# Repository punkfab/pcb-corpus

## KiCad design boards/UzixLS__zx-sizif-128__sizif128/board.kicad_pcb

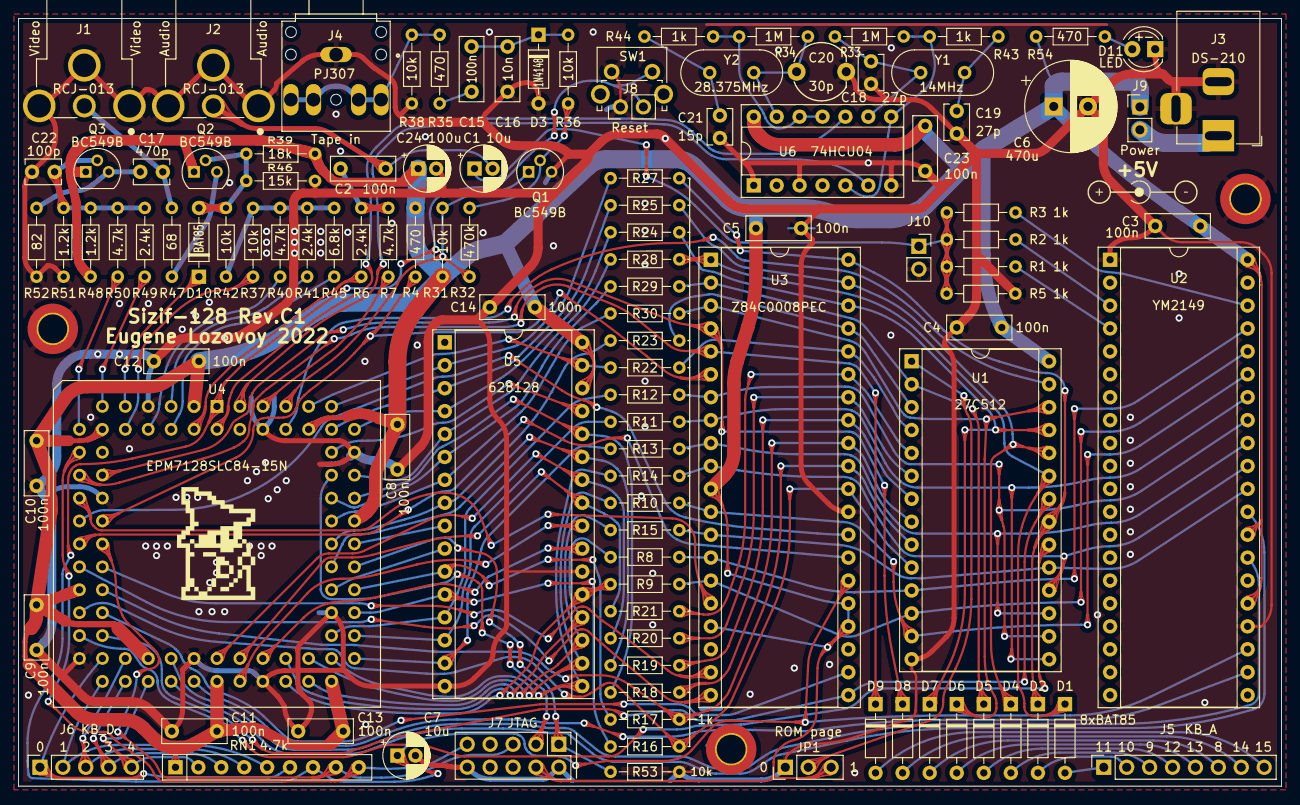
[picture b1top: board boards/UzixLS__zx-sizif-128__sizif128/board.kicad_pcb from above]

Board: 2 copper layers, 140.0 x 85.1 mm, 117 parts (0 on the bottom side), 121 nets.

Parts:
C1, C7: 10u; CP_Radial_D5.0mm_P2.00mm
C2, C3, C4, C5, C8, C9, C10, C11, C12, C13, C14, C15, C23: 100n; C_Disc_D7.0mm_W2.5mm_P5.00mm
C6: 470u; CP_Radial_D10.0mm_P3.80mm
C16: 10n; C_Disc_D7.0mm_W2.5mm_P5.00mm
C17: 470p; C_Disc_D3.8mm_W2.6mm_P2.50mm
C18, C19: 27p; C_Disc_D3.8mm_W2.6mm_P2.50mm
C20: 30p; C_Trim_D6.3mm_P5.50mm
C21: 15p; C_Disc_D3.8mm_W2.6mm_P2.50mm
C22: 100p; C_Disc_D3.8mm_W2.6mm_P2.50mm
C24: 100u; CP_Radial_D5.0mm_P2.00mm
D1, D2, D4, D5, D6, D7, D8, D9, D10: BAT85; D_DO-35_SOD27_P7.62mm_Horizontal
D3: 1N4148; D_DO-35_SOD27_P7.62mm_Horizontal
D11: LED; LED_D4.0mm
H1, H2, H3: MountingHole; MountingHole_3.2mm_M3_DIN965_Pad_TopOnly
J1, J2: RCJ-013; CUI_RCJ-013
J3: DS-210; BarrelJack_Horizontal
J4: PJ307; SWITCHCRAFT_35RAPC4BHN2
J5: Conn_01x08; PinSocket_1x08_P2.54mm_Vertical
J6: Conn_01x05; PinSocket_1x05_P2.54mm_Vertical
J7: Conn_02x05; PinHeader_2x05_P2.54mm_Vertical
J8, J9: Conn_01x02; PinHeader_1x02_P2.54mm_Vertical
J10: Conn_01x02_Female; PinSocket_1x02_P2.54mm_Vertical
JP1: Jumper_3_Bridged12; PinHeader_1x03_P2.54mm_Vertical
LOGO1: logo; black-mage-12.5x8.6-r
LOGO2: logo; dc_center_positive_big
Q1, Q2, Q3: BC549B; TO-92
R1, R2, R3, R5, R8, R9, R10, R11, R12, R13, R14, R15, R16, R17, R18, R19, R20, R21, R22, R23, R24, R25, R27, R28, R29, R30, R43, R44: 1k; R_Axial_DIN0204_L3.6mm_D1.6mm_P7.62mm_Horizontal
R4, R35, R54: 470; R_Axial_DIN0204_L3.6mm_D1.6mm_P7.62mm_Horizontal
R6, R41, R49: 2.4k; R_Axial_DIN0204_L3.6mm_D1.6mm_P7.62mm_Horizontal
R7, R40, R50: 4.7k; R_Axial_DIN0204_L3.6mm_D1.6mm_P7.62mm_Horizontal
R31, R36, R37, R38, R42, R53: 10k; R_Axial_DIN0204_L3.6mm_D1.6mm_P7.62mm_Horizontal
R32: 470k; R_Axial_DIN0204_L3.6mm_D1.6mm_P7.62mm_Horizontal
R33, R34: 1M; R_Axial_DIN0204_L3.6mm_D1.6mm_P7.62mm_Horizontal
R39: 18k; R_Axial_DIN0204_L3.6mm_D1.6mm_P7.62mm_Horizontal
R45: 6.8k; R_Axial_DIN0204_L3.6mm_D1.6mm_P7.62mm_Horizontal
R46: 15k; R_Axial_DIN0204_L3.6mm_D1.6mm_P7.62mm_Horizontal
R47: 68; R_Axial_DIN0204_L3.6mm_D1.6mm_P7.62mm_Horizontal
R48, R51: 1.2k; R_Axial_DIN0204_L3.6mm_D1.6mm_P7.62mm_Horizontal
R52: 82; R_Axial_DIN0204_L3.6mm_D1.6mm_P7.62mm_Horizontal
RN1: 4.7k; R_Array_SIP9
SW1: SW_Push; SW_Tactile_SPST_Angled_PTS645Vx83-2LFS
U1: 27C512; DIP-28_W15.24mm_Socket
U2: YM2149; DIP-40_W15.24mm_Socket
U3: Z84C0008PEC; DIP-40_W15.24mm_Socket
U4: EPM7128SLC84-15N; PLCC-84_THT-Socket
U5: 628128; DIP-32_W15.24mm_Socket
U6: 74HCU04; DIP-14_W7.62mm_Socket
Y1: 14MHz; Crystal_HC49-U_Vertical
Y2: 28.375MHz; Crystal_HC49-U_Vertical

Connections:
+5V: C3.2, C4.2, C5.2, C6.1, C8.2, C9.2, C10.2, C11.2, C12.2, C13.2, C14.2, C23.2, C24.1, J7.4, J9.1, JP1.3 (B), Q2.1 (C), Q3.1 (C), R4.2, R31.1, R39.2, R48.1, R54.1, RN1.1 (common), U1.28 (VCC), U2.25 (A8), U2.28 (BC2), U2.40 (VCC), U3.11 (VCC), U3.17 (~NMI), U3.24 (~WAIT), U3.25 (~BUSRQ), U4.3 (VCCINT), U4.13 (VCCIO), U4.26 (VCCIO), U4.38 (VCCIO), U4.43 (VCCINT), U4.53 (VCCIO), U4.66 (VCCIO), U4.78 (VCCIO), U5.30 (CS2), U5.32 (VCC), U6.14 (VCC)
A0: R16.1, U1.10 (A0), U3.30 (A0), U4.28 (IO)
A1: R17.1, U1.9 (A1), U3.31 (A1), U4.27 (IO)
A2: R18.1, U1.8 (A2), U3.32 (A2)
A3: R19.1, U1.7 (A3), U3.33 (A3)
A4: R20.1, U1.6 (A4), U3.34 (A4)
A5: R21.1, U1.5 (A5), U3.35 (A5)
A6: R22.1, U1.4 (A6), U3.36 (A6)
A7: R23.1, U1.3 (A7), U3.37 (A7)
A8: D7.1 (K), R24.1, U1.25 (A8), U3.38 (A8)
A9: D4.1 (K), R25.1, U1.24 (A9), U3.39 (A9)
A10: D2.1 (K), R27.1, U1.21 (A10), U3.40 (A10)
A11: D1.1 (K), R28.1, U1.23 (A11), U3.1 (A11)
A12: D5.1 (K), R29.1, U1.2 (A12), U3.2 (A12)
A13: D6.1 (K), R30.1, U1.26 (A13), U3.3 (A13)
A14: D8.1 (K), U3.4 (A14), U4.17 (IO)
A15: D9.1 (K), U3.5 (A15), U4.16 (IO)
AY_BC1: U2.29 (BC1), U4.39 (IO)
AY_BDIR: U2.27 (BDIR), U4.40 (IO)
AY_CLK: U2.22 (CLOCK), U4.41 (IO)
BEEPER: R6.1, U4.4 (IO)
Blue: R37.1, U4.10 (IO)
Bright: R45.1, U4.6 (IO)
CHROMA0: R50.1, U4.12 (IO)
CHROMA1: R49.1, U4.11 (IO)
CLK14: U4.83 (INPUT/GCLK1), U6.6
CLKCPU: R4.1, U3.6 (~CLK), U4.21 (IO)
CLK_PAL: U4.2 (INPUT/OE2/GCLK2), U6.10
Csync: D10.1 (K), U4.9 (IO)
D0: R8.1, U1.11 (D0), U2.37 (DA0), U3.14 (D0)
D1: R9.1, U1.12 (D1), U2.36 (DA1), U3.15 (D1)
D2: R10.1, U1.13 (D2), U2.35 (DA2), U3.12 (D2)
D3: R11.1, U1.15 (D3), U2.34 (DA3), U3.8 (D3)
D4: R12.1, U1.16 (D4), U2.33 (DA4), U3.7 (D4)
D5: R13.1, U1.17 (D5), U2.32 (DA5), U3.9 (D5)
D6: R14.1, U1.18 (D6), U2.31 (DA6), U3.10 (D6)
D7: R15.1, U1.19 (D7), U2.30 (DA7), U3.13 (D7)
GND: C3.1, C4.1, C5.1, C6.2, C7.2, C8.1, C9.1, C10.1, C11.1, C12.1, C13.1, C14.1, C16.1, C18.1, C19.1, C20.2, C21.1, C22.2, C23.1, C24.2, D3.2 (A), D11.1 (K), H1.1, H2.1, H3.1, J1.2 (Ext), J2.2 (Ext), J3.2, J3.3, J4.S, J7.2, J7.10, J8.1, J10.2, JP1.1 (A), Q1.3 (E), R5.1, R38.1, R46.2, R51.1, R52.1, R53.1, SW1.1, U1.14 (GND), U2.1 (VSS), U2.24 (~A9), U3.29 (GND), U4.7 (GNDIO), U4.19 (GNDIO), U4.32 (GNDIO), U4.42 (GNDINT), U4.47 (GNDIO), U4.59 (GNDIO), U4.72 (GNDIO), U4.82 (GNDINT), U5.16 (GND), U5.22 (~CS1), U6.1, U6.3, U6.7 (GND)
Green: R41.1, U4.5 (IO)
KD0: J6.1, RN1.6 (R5), U4.34 (IO)
KD1: J6.2, RN1.5 (R4), U4.33 (IO)
KD2: J6.3, RN1.4 (R3), U4.36 (IO)
KD3: J6.4, RN1.3 (R2), U4.35 (IO)
KD4: J6.5, RN1.2 (R1), U4.37 (IO)
unnamed: C1.1, J10.1, R1.2, R2.2, R3.2, R5.2
unnamed: C2.1, R6.2, R7.2
unnamed: C15.1, R35.2
unnamed: C15.2, C16.2, D3.1 (K), R36.1
unnamed: C17.1, Q3.3 (E), R52.2
unnamed: C18.2, R33.1, U6.9, Y1.1
unnamed: C19.2, R43.1, Y1.2
unnamed: C20.1, R34.1, U6.13, Y2.1
unnamed: C21.2, R44.1, Y2.2
unnamed: C22.1, Q3.2 (B), R48.2, R49.2, R50.2, R51.2
unnamed: D1.2 (A), J5.1
unnamed: D2.2 (A), J5.2
unnamed: D4.2 (A), J5.3
unnamed: D5.2 (A), J5.4
unnamed: D6.2 (A), J5.5
unnamed: D7.2 (A), J5.6
unnamed: D8.2 (A), J5.7
unnamed: D9.2 (A), J5.8
unnamed: D10.2 (A), Q2.2 (B), R39.1, R42.2, R46.1
unnamed: D11.2 (A), R54.2
unnamed: J3.1, J9.2
unnamed: JP1.2 (C), U1.1 (A15)
unnamed: Q1.2 (B), R32.2, R36.2
unnamed: Q2.3 (E), R47.2
unnamed: R1.1, U2.4 (A)
unnamed: R2.1, U2.3 (B)
unnamed: R3.1, U2.38 (C)
unnamed: R33.2, R43.2, U6.5, U6.8
unnamed: R34.2, R44.2, U6.11, U6.12
unnamed: R37.2, R40.2, R41.2, R42.1, R45.2
RA14: U1.27 (A14), U4.80 (IO)
Red: R40.1, U4.8 (IO)
SOUND: C1.2, C2.2, J2.1 (In)
TAPE_IN: J4.R, J4.RN, J4.T, J4.TN, R35.1, R38.2
TAPE_IN0: Q1.1 (C), R31.2, R32.1, U4.79 (IO)
TAPE_OUT: R7.1, U4.81 (IO)
TCK: J7.1, R53.2, U4.62 (IO/TCK)
TDI: J7.9, RN1.9 (R8), U4.14 (IO/TDI)
TDO: J7.3, U4.71 (IO/TDO)
TMS: J7.5, RN1.8 (R7), U4.23 (IO/TMS)
VA0: R16.2, U4.58 (IO), U5.12 (A0)
VA1: R17.2, U4.60 (IO), U5.11 (A1)
VA2: R18.2, U4.68 (IO), U5.28 (A13)
VA3: R19.2, U4.63 (IO), U5.27 (A8)
VA4: R20.2, U4.44 (IO), U5.26 (A9)
VA5: R21.2, U4.46 (IO), U5.25 (A11)
VA6: R22.2, U4.77 (IO), U5.31 (A15)
VA7: R23.2, U4.65 (IO), U5.8 (A4)
VA8: R24.2, U4.74 (IO), U5.4 (A12)
VA9: R25.2, U4.76 (IO), U5.3 (A14)
VA10: R27.2, U4.75 (IO), U5.2 (A16)
VA11: R28.2, U4.70 (IO), U5.5 (A7)
VA12: R29.2, U4.69 (IO), U5.6 (A6)
VA13: R30.2, U4.67 (IO), U5.7 (A5)
VA14: U4.61 (IO), U5.10 (A2)
VA15: U4.64 (IO), U5.9 (A3)
VA16: U4.48 (IO), U5.23 (A10)
VD0: R8.2, U4.50 (IO), U5.20 (Q6)
VD1: R9.2, U4.49 (IO), U5.21 (Q7)
VD2: R10.2, U4.52 (IO), U5.18 (Q4)
VD3: R11.2, U4.56 (IO), U5.14 (Q1)
VD4: R12.2, U4.57 (IO), U5.13 (Q0)
VD5: R13.2, U4.54 (IO), U5.15 (Q2)
VD6: R14.2, U4.55 (IO), U5.17 (Q3)
VD7: R15.2, U4.51 (IO), U5.19 (Q5)
VIDEO: C17.2, J1.1 (In), R47.1
nINT: U3.16 (~INT), U4.18 (IO)
nIORQ: U3.20 (~IORQ), U4.24 (IO)
nM1: U3.27 (~M1), U4.22 (IO)
nMREQ: U3.19 (~MREQ), U4.25 (IO)
nRD: U1.22 (~OE), U3.21 (~RD), U4.31 (IO)
nRFSH: U3.28 (~RFSH), U4.20 (IO)
nROMCS: U1.20 (~CE), U4.30 (IO)
nRST: C7.1, J8.2, RN1.7 (R6), SW1.2, U2.23 (~RESET), U3.26 (~RESET), U4.1 (INPUT/GCLRN)
nVRD: U4.45 (IO), U5.24 (~OE)
nVWR: U4.73 (IO), U5.29 (~WE)
nWR: U3.22 (~WR), U4.29 (IO)

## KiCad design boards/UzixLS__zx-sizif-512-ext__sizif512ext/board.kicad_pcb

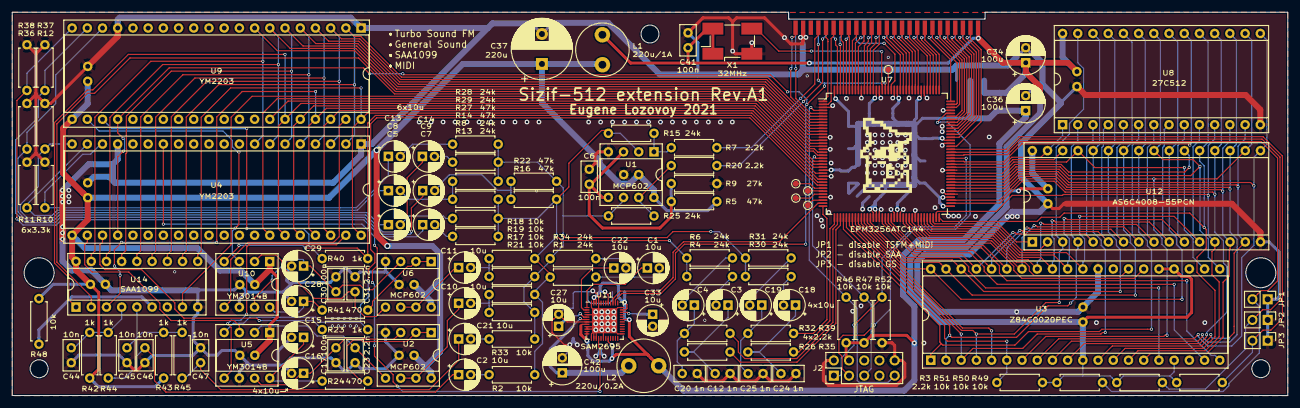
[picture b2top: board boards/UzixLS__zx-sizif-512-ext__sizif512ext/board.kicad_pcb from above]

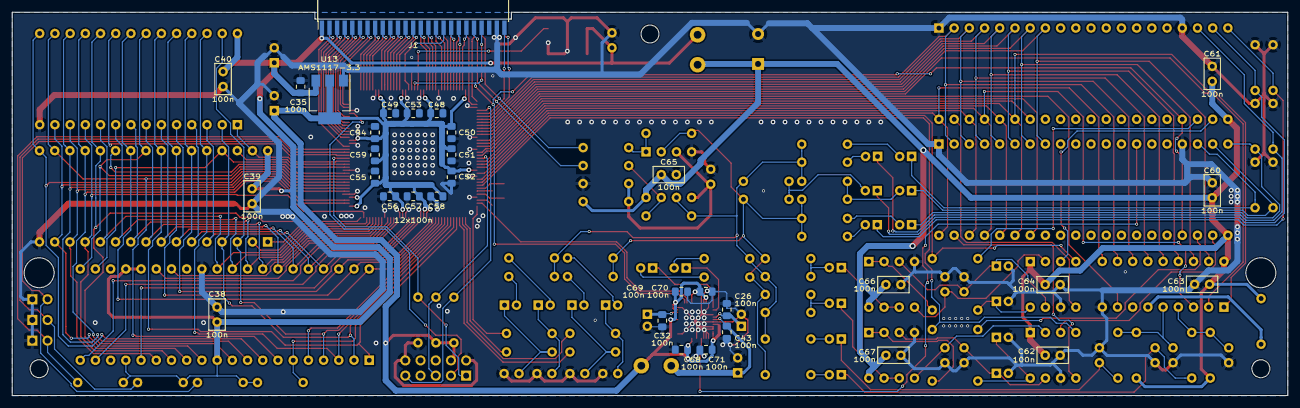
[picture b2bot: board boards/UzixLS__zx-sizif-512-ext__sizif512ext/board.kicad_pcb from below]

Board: 2 copper layers, 213.0 x 64.0 mm, 156 parts (33 on the bottom side), 180 nets.

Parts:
C1, C2, C3, C4, C5, C7, C8, C9, C10, C11, C13, C14, C15, C16, C18, C19, C21, C22, C27, C28, C29, C33: 10u; CP_Radial_D5.0mm_P2.00mm
C6, C17, C30, C38, C39, C40, C41, C60, C61, C62, C63, C64, C65, C66, C67: 100n; C_Disc_D5.0mm_W2.5mm_P2.50mm
C12, C20, C24, C25: 1n; C_Disc_D5.0mm_W2.5mm_P2.50mm
C23, C31: 2.2n; C_Disc_D5.0mm_W2.5mm_P2.50mm
C26, C32, C35, C43, C48, C49, C50, C51, C52, C53, C54, C55, C56, C57, C58, C59, C68, C69, C70, C71: 100n; C_0805_2012Metric_Pad1.15x1.40mm_HandSolder
C34, C36, C42: 100u; CP_Radial_D6.3mm_P2.50mm
C37: 220u; CP_Radial_D10.0mm_P5.00mm
C44, C45, C46, C47: 10n; C_Disc_D5.0mm_W2.5mm_P2.50mm
H1, H2: MountingHole; MountingHole_5mm_7mm_fence
H3, H4, H5: MountingHole; MountingHole_3mm
J1: Conn_02x25_Odd_Even; PinHeader_2x25_P1.27mm_Edge_SMD
J2: PinHeader; PinHeader_2x05_P2.54mm_Vertical
JP1, JP2, JP3: Jumper / Pin header 1x2 Pitch=2.54mm; PinHeader_1x02_P2.54mm_Vertical
L1: 220u/1A; L_Radial_D8.7mm_P5.00mm_Fastron_07HCP
L2: 220u/0.2A; L_Radial_D8.7mm_P5.00mm_Fastron_07HCP
LOGO1: graphic; black-mage2
R1, R4, R6, R8, R13, R15, R25, R28, R29, R30, R31, R34: 24k; R_Axial_DIN0207_L6.3mm_D2.5mm_P7.62mm_Horizontal
R2, R17, R18, R19, R21, R33, R46, R47, R48, R49, R50, R51, R52: 10k; R_Axial_DIN0207_L6.3mm_D2.5mm_P7.62mm_Horizontal
R3, R7, R20, R26, R32, R35, R39: 2.2k; R_Axial_DIN0207_L6.3mm_D2.5mm_P7.62mm_Horizontal
R5, R14, R16, R22, R27: 47k; R_Axial_DIN0207_L6.3mm_D2.5mm_P7.62mm_Horizontal
R9: 27k; R_Axial_DIN0207_L6.3mm_D2.5mm_P7.62mm_Horizontal
R10, R11, R12, R36, R37, R38: 3.3k; R_Axial_DIN0207_L6.3mm_D2.5mm_P7.62mm_Horizontal
R23, R40, R42, R43, R44, R45: 1k; R_Axial_DIN0207_L6.3mm_D2.5mm_P7.62mm_Horizontal
R24, R41: 470; R_Axial_DIN0207_L6.3mm_D2.5mm_P7.62mm_Horizontal
TP1, TP2, TP3, TP4, TP5: TestPoint; TestPoint_Pad_D1.0mm
U1, U2, U6: MCP602; DIP-8_W7.62mm_Socket
U3: Z84C0020PEC; DIP-40_W15.24mm_Socket
U4, U9: YM2203; DIP-40_W15.24mm_Socket
U5, U10: YM3014B; DIP-8_W7.62mm_Socket
U7: EPM3256ATC144; TQFP-144_20x20mm_P0.5mm
U8: 27C512; DIP-28_W15.24mm_Socket
U11: SAM2695; QFN-48-1EP_6x6mm_P0.4mm_EP4.2x4.2mm
U12: AS6C4008-55PCN; DIP-32_W15.24mm_Socket
U13: AMS1117-3.3; SOT-223-3_TabPin2
U14: SAA1099; DIP-18_W7.62mm_Socket
X1: 32MHz; Oscillator_SMD_EuroQuartz_XO91-4Pin_7.0x5.0mm_HandSoldering

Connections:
+3.3VA: C42.1, C43.1, L2.2, U11.6 (VA33)
+3V3: C36.1, C48.1, C49.1, C50.1, C51.1, C52.1, C53.1, C54.1, C55.1, C56.1, C57.1, C58.1, C59.1, C68.1, C69.1, C70.1, C71.1, J2.4, L2.1, R46.2, R47.2, U7.24 (VCCIO), U7.50 (VCCIO), U7.51 (VCCINT), U7.58 (VCCINT), U7.73 (VCCIO), U7.76 (VCCIO), U7.95 (VCCIO), U7.115 (VCCIO), U7.123 (VCCINT), U7.130 (VCCINT), U7.144 (VCCIO), U11.8 (VD33), U11.11 (VD33), U11.12 (~WR), U11.20 (VD33), U11.31 (VD33), U11.35 (VD33), U11.41 (VD33), U11.46 (VD33), U11.47 (XDIV), U13.2 (VO)
+5V: C34.1, C35.2, C38.2, C39.2, C40.2, C41.2, J1.1, J1.2, L1.1, R3.1, R49.1, R50.1, R51.1, U3.11 (VCC), U3.17 (~NMI~), U3.24 (~WAIT~), U3.25 (~BUSRQ~), U8.28 (VCC), U12.32 (VCC), U13.3 (VI), X1.1 (EN), X1.4 (V+)
+5VA: C37.1, C60.2, C61.2, C62.2, C63.2, C64.2, C65.2, C66.2, C67.2, L1.2, R5.2, R42.2, R43.2, R48.2, U1.8 (V+), U2.8 (V+), U4.21 (VDD), U5.1 (Vdd), U6.8 (V+), U9.21 (VDD), U10.1 (Vdd), U14.18 (VCC)
/A0: J1.36, U7.139 (IO)
/A1: J1.34, U7.138 (IO)
/A2: J1.31, U7.137 (IO)
/A3: J1.32, U7.136 (IO)
/A4: J1.29, U7.134 (IO)
/A5: J1.35, U7.140 (IO)
/A6: J1.30, U7.133 (IO)
/A7: J1.27, U7.132 (IO)
/A8: J1.5, U7.98 (IO)
/A9: J1.10, U7.101 (IO)
/A10: J1.12, U7.103 (IO)
/A11: J1.9, U7.102 (IO)
/A12: J1.7, U7.100 (IO)
/A13: J1.19, U7.116 (IO)
/A14: J1.23, U7.120 (IO)
/A15: J1.24, U7.119 (IO)
/AA0: U4.37 (A0), U7.23 (IO), U9.37 (A0), U14.3 (A0)
/AD0: U4.40 (D0), U7.27 (IO), U9.40 (D0), U14.10 (D0)
/AD1: U4.2 (D1), U7.7 (IO), U9.2 (D1), U14.11 (D1)
/AD2: U4.3 (D2), U7.8 (IO), U9.3 (D2), U14.12 (D2)
/AD3: U4.4 (D3), U7.9 (IO), U9.4 (D3), U14.13 (D3)
/AD4: U4.5 (D4), U7.10 (IO), U9.5 (D4), U14.14 (D4)
/AD5: U4.6 (D5), U7.11 (IO), U9.6 (D5), U14.15 (D5)
/AD6: U4.7 (D6), U7.12 (IO), U9.7 (D6), U14.16 (D6)
/AD7: U4.8 (D7), U7.14 (IO), U9.8 (D7), U14.17 (D7)
/AY_A1: C5.1, R12.2, U4.20 (A)
/AY_A2: C7.1, R38.2, U9.20 (A)
/AY_B1: C8.1, R11.2, U4.19 (B)
/AY_B2: C9.1, R37.2, U9.19 (B)
/AY_C1: C13.1, R10.2, U4.18 (C)
/AY_C2: C14.1, R36.2, U9.18 (C)
/BUS0: J1.50, U7.6 (IO)
/BUS1: J1.49, U7.5 (IO)
/CFG0: JP1.2, R51.2, U7.90 (IO)
/CFG1: JP2.2, R50.2, U7.91 (IO)
/CFG2: JP3.2, R49.2, U7.92 (IO)
/CLK32: U7.128 (IN/OE2/GCLK2), X1.3 (OUT)
/CLKCPU: J1.33, U7.125 (IN/GCLK1)
/D0: J1.38, U7.141 (IO)
/D1: J1.37, U7.142 (IO)
/D2: J1.40, U7.2 (IO)
/D3: J1.21, U7.118 (IO)
/D4: J1.22, U7.117 (IO)
/D5: J1.17, U7.112 (IO)
/D6: J1.15, U7.110 (IO)
/D7: J1.13, U7.108 (IO)
/FM1: C10.1, U2.6 (-), U2.7
/FM1_ENA: R23.2, U5.4 (SD), U7.29 (IO)
/FM2: C11.1, U6.6 (-), U6.7
/FM2_ENA: R40.2, U7.28 (IO), U10.4 (SD)
/GA0: U3.30 (A0), U7.68 (IO), U8.10 (A0), U12.12 (A0)
/GA1: U3.31 (A1), U7.67 (IO), U8.9 (A1), U12.11 (A1)
/GA2: U3.32 (A2), U7.66 (IO), U8.8 (A2), U12.10 (A2)
/GA3: U3.33 (A3), U7.65 (IO), U8.7 (A3), U12.9 (A3)
/GA4: U3.34 (A4), U7.62 (IO), U8.6 (A4), U12.8 (A4)
/GA5: U3.35 (A5), U7.60 (IO), U8.5 (A5), U12.7 (A5)
/GA6: U3.36 (A6), U7.55 (IO), U8.4 (A6), U12.6 (A6)
/GA7: U3.37 (A7), U7.53 (IO), U8.3 (A7), U12.5 (A7)
/GA8: U3.38 (A8), U7.48 (IO), U8.25 (A8), U12.27 (A8)
/GA9: U3.39 (A9), U7.47 (IO), U8.24 (A9), U12.26 (A9)
/GA10: U3.40 (A10), U7.46 (IO), U8.21 (A10), U12.23 (A10)
/GA11: U3.1 (A11), U7.40 (IO), U8.23 (A11), U12.25 (A11)
/GA12: U3.2 (A12), U7.42 (IO), U8.2 (A12), U12.4 (A12)
/GA13: U3.3 (A13), U7.43 (IO), U8.26 (A13), U12.28 (A13)
/GA14: U3.4 (A14), U7.44 (IO), U8.27 (A14), U12.3 (A14)
/GA15: U3.5 (A15), U7.45 (IO)
/GCH0: C3.1, C12.1, R26.1
/GCH1: C4.1, C20.1, R32.1
/GCH2: C18.1, C24.1, R35.1
/GCH3: C19.1, C25.1, R39.1
/GCLK: R3.2, U3.6 (~CLK~), U7.41 (IO)
/GD0: U3.14 (D0), U7.71 (IO), U8.11 (D0), U12.13 (D0)
/GD1: U3.15 (D1), U7.75 (IO), U8.12 (D1), U12.14 (D1)
/GD2: U3.12 (D2), U7.79 (IO), U8.13 (D2), U12.15 (D2)
/GD3: U3.8 (D3), U7.80 (IO), U8.15 (D3), U12.17 (D3)
/GD4: U3.7 (D4), U7.81 (IO), U8.16 (D4), U12.18 (D4)
/GD5: U3.9 (D5), U7.78 (IO), U8.17 (D5), U12.19 (D5)
/GD6: U3.10 (D6), U7.74 (IO), U8.18 (D6), U12.20 (D6)
/GD7: U3.13 (D7), U7.72 (IO), U8.19 (D7), U12.21 (D7)
/GDAC0: R26.2, U7.39 (IO)
/GDAC1: R32.2, U7.38 (IO)
/GDAC2: R35.2, U7.37 (IO)
/GDAC3: R39.2, U7.36 (IO)
/GMA15: U7.87 (IO), U8.1 (A15), U12.31 (A15)
/GMA16: U7.69 (IO), U12.2 (A16)
/GMA17: U7.70 (IO), U12.1 (A18)
/GMA18: U7.86 (IO), U12.30 (A17)
/MIDI_CLK: U7.35 (IO), U11.39 (X1)
/MIDI_IN: U4.14 (IOA2), U11.16 (MIDI_IN)
/MIDI_L: C1.1, U11.1 (AOUTL)
/MIDI_R: C22.1, U11.2 (AOUTR)
/MIX_L: J1.44, R7.1
/MIX_R: J1.41, R20.1
/SAA_CLK: U7.16 (IO), U14.8 (CLK)
/SAA_L: C2.1, C46.1, R44.2
/SAA_R: C21.1, C47.1, R45.2
/TCK: J2.1, R52.1, U7.89 (TCK)
/TDI: J2.9, R46.1, U7.4 (TDI)
/TDO: J2.3, U7.104 (TDO)
/TMS: J2.5, R47.1, U7.20 (TMS)
/YM_M: U4.38 (M), U7.25 (IO), U9.38 (M)
/~ARD: U4.36 (~RD~), U7.22 (IO), U9.36 (~RD~)
/~AWR: U4.35 (~WR~), U7.21 (IO), U9.35 (~WR~), U14.1 (~WR)
/~BUSACK: J1.4, U7.93 (IO)
/~BUSRQ: J1.6, U7.97 (IO)
/~GINT: U3.16 (~INT~), U7.49 (IO)
/~GIORQ: U3.20 (~IORQ~), U7.56 (IO)
/~GM1: U3.27 (~M1~), U7.63 (IO)
/~GMREQ: U3.19 (~MREQ~), U7.54 (IO)
/~GRAM: U7.83 (IO), U12.22 (~CE)
/~GRD: U3.21 (~RD~), U7.82 (IO), U8.22 (~OE), U12.24 (~OE)
/~GRESET: U3.26 (~RESET~), U7.61 (IO)
/~GROM: U7.88 (IO), U8.20 (~CE)
/~GWR: U3.22 (~WR~), U7.84 (IO), U12.29 (~WE)
/~HALT: J1.3, U7.96 (IO)
/~INT: J1.39, U7.143 (IO)
/~IORQ: J1.14, U7.107 (IO)
/~IORQGE: J1.20, U7.113 (IO)
/~M1: J1.26, U7.121 (IO)
/~MREQ: J1.28, U7.131 (IO)
/~NMI: J1.42, U7.1 (IO)
/~RD: J1.18, U7.111 (IO)
/~RFSH: J1.25, U7.122 (IO)
/~ROMCSB: J1.11, U7.106 (IO)
/~RST: J1.43, U4.24 (~IC~), U7.127 (IN/GCLRn), U9.24 (~IC~), U11.38 (~RST~/~PD~)
/~SAA_CS: U7.15 (IO), U14.2 (~CS)
/~WAIT: J1.8, U7.99 (IO)
/~WR: J1.16, U7.109 (IO)
/~YM1_CS: U4.34 (~CS~), U7.18 (IO)
/~YM2_CS: U7.19 (IO), U9.34 (~CS~)
GND: C6.1, C12.2, C15.2, C16.2, C17.2, C20.2, C23.2, C24.2, C25.2, C26.2, C27.2, C28.2, C29.2, C30.2, C31.2, C32.2, C33.2, C34.2, C35.1, C36.2, C37.2, C38.1, C39.1, C40.1, C41.1, C42.2, C43.2, C44.2, C45.2, C46.2, C47.2, C48.2, C49.2, C50.2, C51.2, C52.2, C53.2, C54.2, C55.2, C56.2, C57.2, C58.2, C59.2, C60.1, C61.1, C62.1, C63.1, C64.1, C65.1, C66.1, C67.1, C68.2, C69.2, C70.2, C71.2, J1.47, J1.48, J2.2, J2.10, JP1.1, JP2.1, JP3.1, R9.2, R10.1, R11.1, R12.1, R36.1, R37.1, R38.1, R52.2, U1.4 (V-), U2.4 (V-), U3.29 (GND), U4.1 (GND), U4.17 (AGND), U5.6 (Vss), U6.4 (V-), U7.3 (GNDIO), U7.13 (GNDIO), U7.17 (GNDIO), U7.26 (GNDIO), U7.33 (GNDIO), U7.52 (GNDINT), U7.57 (GNDINT), U7.59 (GNDIO), U7.64 (GNDIO), U7.77 (GNDIO), U7.85 (GNDIO), U7.94 (GNDIO), U7.105 (GNDIO), U7.114 (GNDIO), U7.124 (GNDINT), U7.129 (GNDINT), U7.135 (GNDIO), U8.14 (GND), U9.1 (GND), U9.17 (AGND), U10.6 (Vss), U11.4 (AGND), U11.7 (MICIN), U11.9 (GND), U11.10 (A0), U11.13 (GND), U11.14 (~CS), U11.15 (~RD), U11.18 (GND), U11.25 (GND), U11.36 (GND), U11.45 (GND), U11.48 (GND), U11.49 (GND), U12.16 (GND), U13.1 (GND), U14.9 (GND), X1.2 (GND)
unnamed: C1.2, R1.2
unnamed: C2.2, R2.2
unnamed: C3.2, R4.2
unnamed: C4.2, R6.2
unnamed: C5.2, R8.2
unnamed: C6.2, R5.1, R9.1, U1.3 (+), U1.5 (+)
unnamed: C7.2, R13.2
unnamed: C8.2, R14.2, R27.2
unnamed: C9.2, R16.2, R22.2
unnamed: C10.2, R17.2, R21.2
unnamed: C11.2, R18.2, R19.2
unnamed: C13.2, R28.2
unnamed: C14.2, R29.2
unnamed: C15.1, R24.2, U5.8 (Mp)
unnamed: C16.1, C17.1, U2.3 (+), U5.7 (Rb)
unnamed: C18.2, R30.2
unnamed: C19.2, R31.2
unnamed: C21.2, R33.2
unnamed: C22.2, R34.2
unnamed: C23.1, U2.5 (+), U5.2 (ToBUFF)
unnamed: C26.1, C27.1, U11.5 (VCM)
unnamed: C28.1, R41.2, U10.8 (Mp)
unnamed: C29.1, C30.1, U6.3 (+), U10.7 (Rb)
unnamed: C31.1, U6.5 (+), U10.2 (ToBUFF)
unnamed: C32.1, C33.1, U11.34 (OUTVC12)
unnamed: C44.1, R42.1, R44.1, U14.4 (OutL)
unnamed: C45.1, R43.1, R45.1, U14.5 (OutR)
unnamed: R1.1, R2.1, R4.1, R6.1, R8.1, R13.1, R14.1, R15.1, R16.1, R17.1, R18.1, U1.2 (-)
unnamed: R7.2, R15.2, U1.1
unnamed: R19.1, R21.1, R22.1, R25.1, R27.1, R28.1, R29.1, R30.1, R31.1, R33.1, R34.1, U1.6 (-)
unnamed: R20.2, R25.2, U1.7
unnamed: R23.1, U4.23 (OP-O)
unnamed: R24.1, U2.1, U2.2 (-)
unnamed: R40.1, U9.23 (OP-O)
unnamed: R41.1, U6.1, U6.2 (-)
unnamed: R48.1, U14.6 (Iref)
unnamed: TP1.1, U7.126 (IN/OE1)
unnamed: TP2.1, U7.30 (IO)
unnamed: TP3.1, U7.31 (IO)
unnamed: TP4.1, U7.32 (IO)
unnamed: TP5.1, U7.34 (IO)
unnamed: U4.22 (SH), U5.3 (LOAD)
unnamed: U4.39 (S), U5.5 (CLOCK)
unnamed: U9.22 (SH), U10.3 (LOAD)
unnamed: U9.39 (S), U10.5 (CLOCK)

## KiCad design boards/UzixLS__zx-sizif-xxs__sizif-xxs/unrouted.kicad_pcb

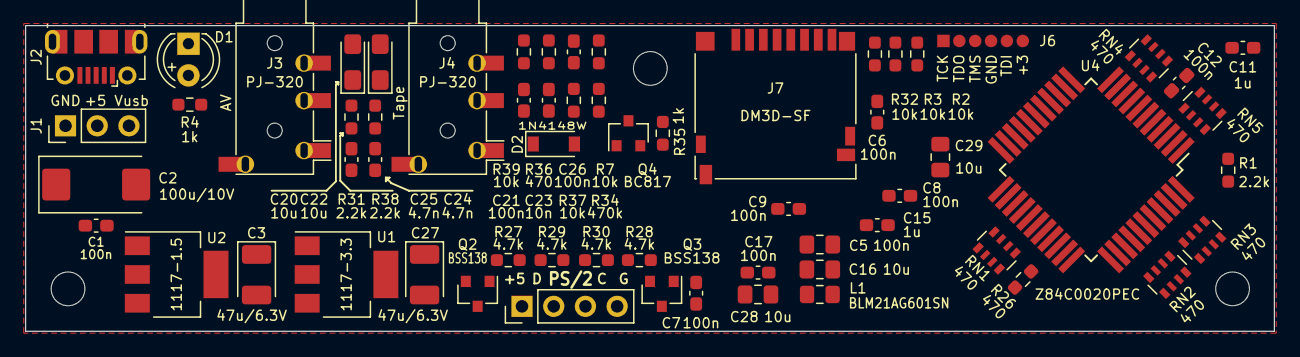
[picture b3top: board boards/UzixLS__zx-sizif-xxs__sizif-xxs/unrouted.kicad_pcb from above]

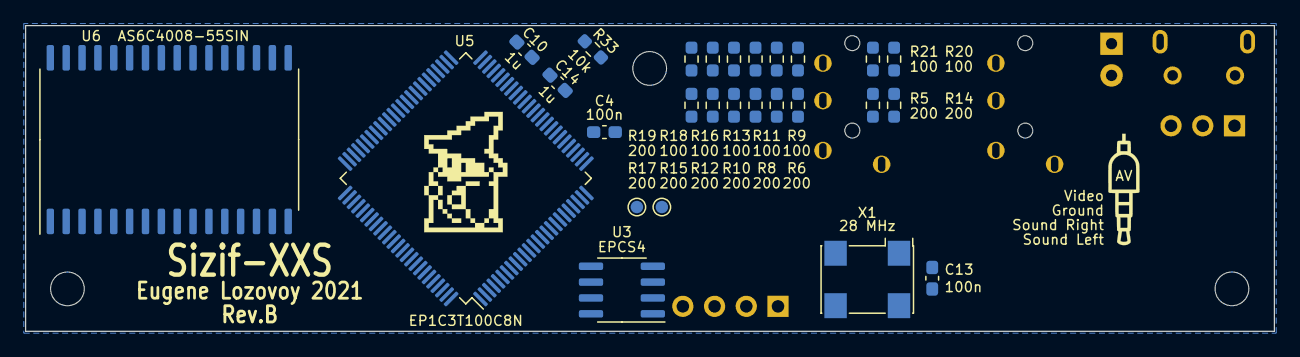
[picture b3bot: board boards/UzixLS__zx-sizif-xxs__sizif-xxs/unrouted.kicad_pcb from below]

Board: 2 copper layers, 100.0 x 24.5 mm, 94 parts (29 on the bottom side), 123 nets, no tracks yet.

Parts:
C1, C4, C6, C7, C8, C9, C12, C13, C17, C21, C26: 100n; C_0603_1608Metric_Pad1.08x0.95mm_HandSolder
C2: 100u/10V; CP_EIA-7343-31_Kemet-D_Pad2.25x2.55mm_HandSolder
C3, C27: 47u/6.3V; CP_EIA-3528-21_Kemet-B_Pad1.50x2.35mm_HandSolder
C5: 100n; C_0805_2012Metric_Pad1.18x1.45mm_HandSolder
C10, C11, C14, C15: 1u; C_0603_1608Metric_Pad1.08x0.95mm_HandSolder
C16, C28, C29: 10u; C_0805_2012Metric_Pad1.18x1.45mm_HandSolder
C20, C22: 10u; CP_EIA-3216-18_Kemet-A_Pad1.58x1.35mm_HandSolder
C23: 10n; C_0603_1608Metric_Pad1.08x0.95mm_HandSolder
C24, C25: 4.7n; C_0603_1608Metric_Pad1.08x0.95mm_HandSolder
D1: LED; LED_D4.0mm
D2: 1N4148W; D_SOD-123
H1, H2, H3: MountingHole; MountingHole_2.7mm_M2.5_dk5.0mm_Mask
J1: Pin header 1x3 Pitch=2.54mm; PinHeader_1x03_P2.54mm_Vertical
J2: USB_B_Micro; USB_Micro-B_Molex-105017-0001
J3, J4: PJ-320; PJ-320A_D
J5: Pin header 1x4 Pitch=2.54mm; PinHeader_1x04_P2.54mm_Vertical
J6: Solder joints; PinPoints_1x06_P1.27mm
J7: DM3D-SF; microSD_HC_Hirose_DM3D-SF
L1: BLM21AG601SN; L_0805_2012Metric_Pad1.15x1.40mm_HandSolder
LOGO1: graphic; black-mage-9.6x6.5
LOGO2: Jack35; jack35_4pin
Q2, Q3: BSS138; SOT-23
Q4: BC817; SOT-23
R1, R31, R38: 2.2k; R_0603_1608Metric_Pad0.98x0.95mm_HandSolder
R2, R3, R7, R32, R33, R37, R39: 10k; R_0603_1608Metric_Pad0.98x0.95mm_HandSolder
R4, R35: 1k; R_0603_1608Metric_Pad0.98x0.95mm_HandSolder
R5, R6, R8, R10, R12, R14, R15, R17, R19: 200; R_0603_1608Metric_Pad0.98x0.95mm_HandSolder
R9, R11, R13, R16, R18, R20, R21: 100; R_0603_1608Metric_Pad0.98x0.95mm_HandSolder
R26, R36: 470; R_0603_1608Metric_Pad0.98x0.95mm_HandSolder
R27, R28, R29, R30: 4.7k; R_0603_1608Metric_Pad0.98x0.95mm_HandSolder
R34: 470k; R_0603_1608Metric_Pad0.98x0.95mm_HandSolder
RN1, RN2, RN3, RN4, RN5: 470; R_Array_Convex_4x0603
TP1, TP2: TestPoint; TestPoint_Pad_D1.0mm
U1: 1117-3.3; SOT-223-3_TabPin2
U2: 1117-1.5; SOT-223-3_TabPin2
U3: EPCS4; SOIC-8_3.9x4.9mm_P1.27mm
U4: Z84C0020PEC; TQFP-44_14x14mm_P0.8mm
U5: EP1C3T100C8N; TQFP-100_14x14mm_P0.5mm
U6: AS6C4008-55SIN; SSOP-32_11.305x20.495mm_P1.27mm
X1: 28 MHz; Oscillator_SMD_SeikoEpson_SG8002CA-4Pin_7.0x5.0mm

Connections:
1V5_PLL: C17.2, C28.2, L1.2, U5.9 (VCCA_PLL1)
+1V5: C3.1, C14.1, C15.2, L1.1, U2.2 (VO), U5.33 (VCCINT), U5.44 (VCCINT), U5.82 (VCCINT), U5.93 (VCCINT)
+3V3: C4.2, C5.2, C6.1, C7.1, C8.1, C9.1, C10.1, C11.1, C12.1, C13.1, C16.2, C27.1, C29.2, J6.6, J7.4 (VDD), Q2.1 (G), Q3.1 (G), R1.2, R2.1, R3.1, R27.2, R28.2, R32.1, R33.1, R34.2, U1.2 (VO), U3.3 (VCC), U3.7 (VCC), U3.8 (VCC), U4.6 (VCC), U4.21 (~WAIT~), U4.22 (~BUSRQ~), U5.8 (nCONFIG), U5.18 (VCCIO1), U5.31 (VCCIO4), U5.46 (VCCIO4), U5.59 (VCCIO3), U5.80 (VCCIO2), U5.95 (VCCIO2), U6.32 (VCC), X1.1 (EN), X1.4 (V+)
+5V: C1.2, C2.1, D1.2 (A), J1.2, J5.1, R29.2, R30.2, U1.3 (VI), U2.3 (VI)
/A0: RN1.8 (R1.2), U4.27 (A0)
/A1: RN1.7 (R2.2), U4.28 (A1)
/A2: RN1.6 (R3.2), U4.29 (A2)
/A3: RN1.5 (R4.2), U4.30 (A3)
/A4: R26.2, U4.31 (A4)
/A5: RN2.8 (R1.2), U4.32 (A5)
/A6: RN2.7 (R2.2), U4.34 (A6)
/A7: RN2.6 (R3.2), U4.35 (A7)
/A8: RN2.5 (R4.2), U4.36 (A8)
/A9: RN3.8 (R1.2), U4.37 (A9)
/A10: RN3.7 (R2.2), U4.38 (A10)
/A11: RN3.6 (R3.2), U4.40 (A11)
/A12: RN3.5 (R4.2), U4.41 (A12)
/A13: U4.42 (A13), U5.78 (IO)
/A14: U4.43 (A14), U5.76 (IO)
/A15: U4.44 (A15), U5.77 (IO)
/CLK: U5.10 (CLK0), X1.3 (OUT)
/CLKCPU: R1.1, U4.1 (~CLK~), U5.73 (IO)
/D0: RN4.6 (R3.2), U4.9 (D0)
/D1: RN4.5 (R4.2), U4.10 (D1)
/D2: RN4.8 (R1.2), U4.7 (D2)
/D3: RN5.7 (R2.2), U4.3 (D3)
/D4: RN5.8 (R1.2), U4.2 (D4)
/D5: RN5.6 (R3.2), U4.4 (D5)
/D6: RN5.5 (R4.2), U4.5 (D6)
/D7: RN4.7 (R2.2), U4.8 (D7)
/EPCS_ASD: U3.5 (ASDI), U5.17 (IO/ASDO)
/EPCS_DATA: U3.2 (DATA), U5.7 (DATA0)
/EPCS_DCLK: U3.6 (DCLK), U5.16 (DCLK)
/PS2_CLK: Q3.2 (S), R28.1, U5.20 (IO)
/PS2_DAT: Q2.2 (S), R27.1, U5.21 (IO)
/SD_MISO\TAPE: J7.7 (DAT0), R35.2, U5.40 (IO)
/SD_MOSI\TAPE: J7.3 (CMD), R7.1, U5.42 (IO)
/SD_SCK: J7.5 (CLK), U5.41 (IO)
/SND_DAC_L: R31.1, U5.24 (IO)
/SND_DAC_R: R38.1, U5.25 (IO)
/SND_L: C20.2, J3.T
/SND_R: C22.2, J3.R1
/TAPE_IN: J4.T, R36.1, R39.1
/TAPE_OUT: C26.1, J4.R1
/TCK: J6.1, U5.62 (TCK)
/TDI: J6.5, U5.67 (TDI)
/TDO: J6.2, U5.64 (TDO)
/TMS: J6.3, U5.63 (TMS)
/V0: R17.1, U5.37 (IO)
/V1: R15.1, U5.36 (IO)
/V2: R12.1, U5.35 (IO)
/V3: R10.1, U5.34 (IO)
/V4: R8.1, U5.29 (IO)
/V5: R6.1, U5.28 (IO)
/V6: R5.1, U5.27 (IO)
/V7: R14.1, U5.26 (IO)
/VA0: RN1.1 (R1.1), U5.88 (IO), U6.12 (A0)
/VA1: RN1.2 (R2.1), U5.89 (IO), U6.11 (A1)
/VA2: RN1.3 (R3.1), U5.90 (IO), U6.10 (A2)
/VA3: RN1.4 (R4.1), U5.91 (IO), U6.9 (A3)
/VA4: R26.1, U5.92 (IO), U6.8 (A4)
/VA5: RN2.1 (R1.1), U5.2 (IO/CRC_ERROR), U6.7 (A5)
/VA6: RN2.2 (R2.1), U5.97 (IO), U6.6 (A6)
/VA7: RN2.3 (R3.1), U5.98 (IO), U6.5 (A7)
/VA8: RN2.4 (R4.1), U5.99 (IO/DEV_OE), U6.31 (A15)
/VA9: RN3.1 (R1.1), U5.100 (IO/DEV_CLRn), U6.4 (A12)
/VA10: RN3.2 (R2.1), U5.1 (IO/INIT_DONE), U6.2 (A16)
/VA11: RN3.3 (R3.1), U5.5 (IO), U6.3 (A14)
/VA12: RN3.4 (R4.1), U5.4 (IO), U6.1 (A18)
/VA13: U5.70 (IO), U6.28 (A13)
/VA14: U5.56 (IO), U6.23 (A10)
/VA15: U5.69 (IO), U6.27 (A8)
/VA16: U5.65 (IO), U6.25 (A11)
/VA17: U5.72 (IO), U6.30 (A17)
/VA18: U5.68 (IO), U6.26 (A9)
/VD0: RN4.3 (R3.1), U5.48 (IO), U6.21 (D7)
/VD1: RN4.4 (R4.1), U5.50 (IO), U6.20 (D6)
/VD2: RN4.1 (R1.1), U5.47 (IO), U6.18 (D4)
/VD3: RN5.2 (R2.1), U5.87 (IO), U6.14 (D1)
/VD4: RN5.1 (R1.1), U5.3 (IO/CLKUSR), U6.13 (D0)
/VD5: RN5.3 (R3.1), U5.79 (IO), U6.15 (D2)
/VD6: RN5.4 (R4.1), U5.51 (IO), U6.17 (D3)
/VD7: RN4.2 (R2.1), U5.49 (IO), U6.19 (D5)
/Video: J3.S, R14.2, R20.2
/~EPCS_CS: U3.1 (~CS), U5.6 (IO/nCSO)
/~INT: U4.12 (~INT~), U5.54 (IO)
/~IORQ: U4.16 (~IORQ~), U5.53 (IO)
/~M1: U4.24 (~M1~), U5.85 (IO)
/~MREQ: U4.15 (~MREQ~), U5.52 (IO)
/~NMI: U4.13 (~NMI~), U5.55 (IO)
/~RD: U4.18 (~RD~), U5.75 (IO)
/~RFSH: U4.25 (~RFSH~), U5.86 (IO)
/~RSTCPU: U4.23 (~RESET~), U5.84 (IO)
/~SD_CD: J7.9 (DET_B), U5.38 (IO)
/~SD_CS: J7.2 (DAT3/CD), U5.39 (IO)
/~VRD: U5.57 (IO), U6.24 (~OE)
/~VWR: U5.71 (IO), U6.29 (~WE)
/~WR: U4.19 (~WR~), U5.74 (IO)
GND: C1.1, C2.2, C3.2, C4.1, C5.1, C6.2, C7.2, C8.2, C9.2, C10.2, C11.2, C12.2, C13.2, C14.2, C15.1, C16.1, C17.1, C23.2, C24.2, C25.2, C27.2, C28.1, C29.1, D2.2 (A), J1.1, J2.5 (GND), J2.6 (Shield), J3.R2, J4.R2, J4.S, J5.4, J6.4, J7.6 (VSS), J7.10 (DET_A), J7.11 (SHIELD), Q4.2 (E), R4.2, R19.1, R39.2, U1.1 (GND), U2.1 (GND), U3.4 (GND), U4.26 (GND), U5.11 (GNDA_PLL1), U5.13 (nCE), U5.14 (MSEL0), U5.15 (MSEL1), U5.19 (GND), U5.30 (GND), U5.32 (GND), U5.43 (GND), U5.45 (GND), U5.58 (GND), U5.81 (GND), U5.83 (GND), U5.94 (GND), U5.96 (GND), U6.16 (GND), U6.22 (~CE), X1.2 (GND)
unnamed: C20.1, C25.1, R31.2
unnamed: C21.1, C23.1, D2.1 (K), R37.1
unnamed: C21.2, R36.2
unnamed: C22.1, C24.1, R38.2
unnamed: C26.2, R7.2
unnamed: D1.1 (K), R4.1
unnamed: J1.3, J2.1 (VBUS)
unnamed: J5.2, Q2.3 (D), R29.1
unnamed: J5.3, Q3.3 (D), R30.1
unnamed: J7.1 (DAT2), R33.2
unnamed: J7.8 (DAT1), R32.2
unnamed: Q4.1 (B), R34.1, R37.2
unnamed: Q4.3 (C), R35.1
unnamed: R2.2, U5.61 (nSTATUS)
unnamed: R3.2, U5.60 (CONF_DONE)
unnamed: R10.2, R11.1, R13.2
unnamed: R8.2, R9.1, R11.2
unnamed: R12.2, R13.1, R16.2
unnamed: R15.2, R16.1, R18.2
unnamed: R17.2, R18.1, R19.2
unnamed: R5.2, R20.1, R21.2
unnamed: R6.2, R9.2, R21.1
unnamed: TP1.1, U5.22 (IO)
unnamed: TP2.1, U5.23 (IO)
